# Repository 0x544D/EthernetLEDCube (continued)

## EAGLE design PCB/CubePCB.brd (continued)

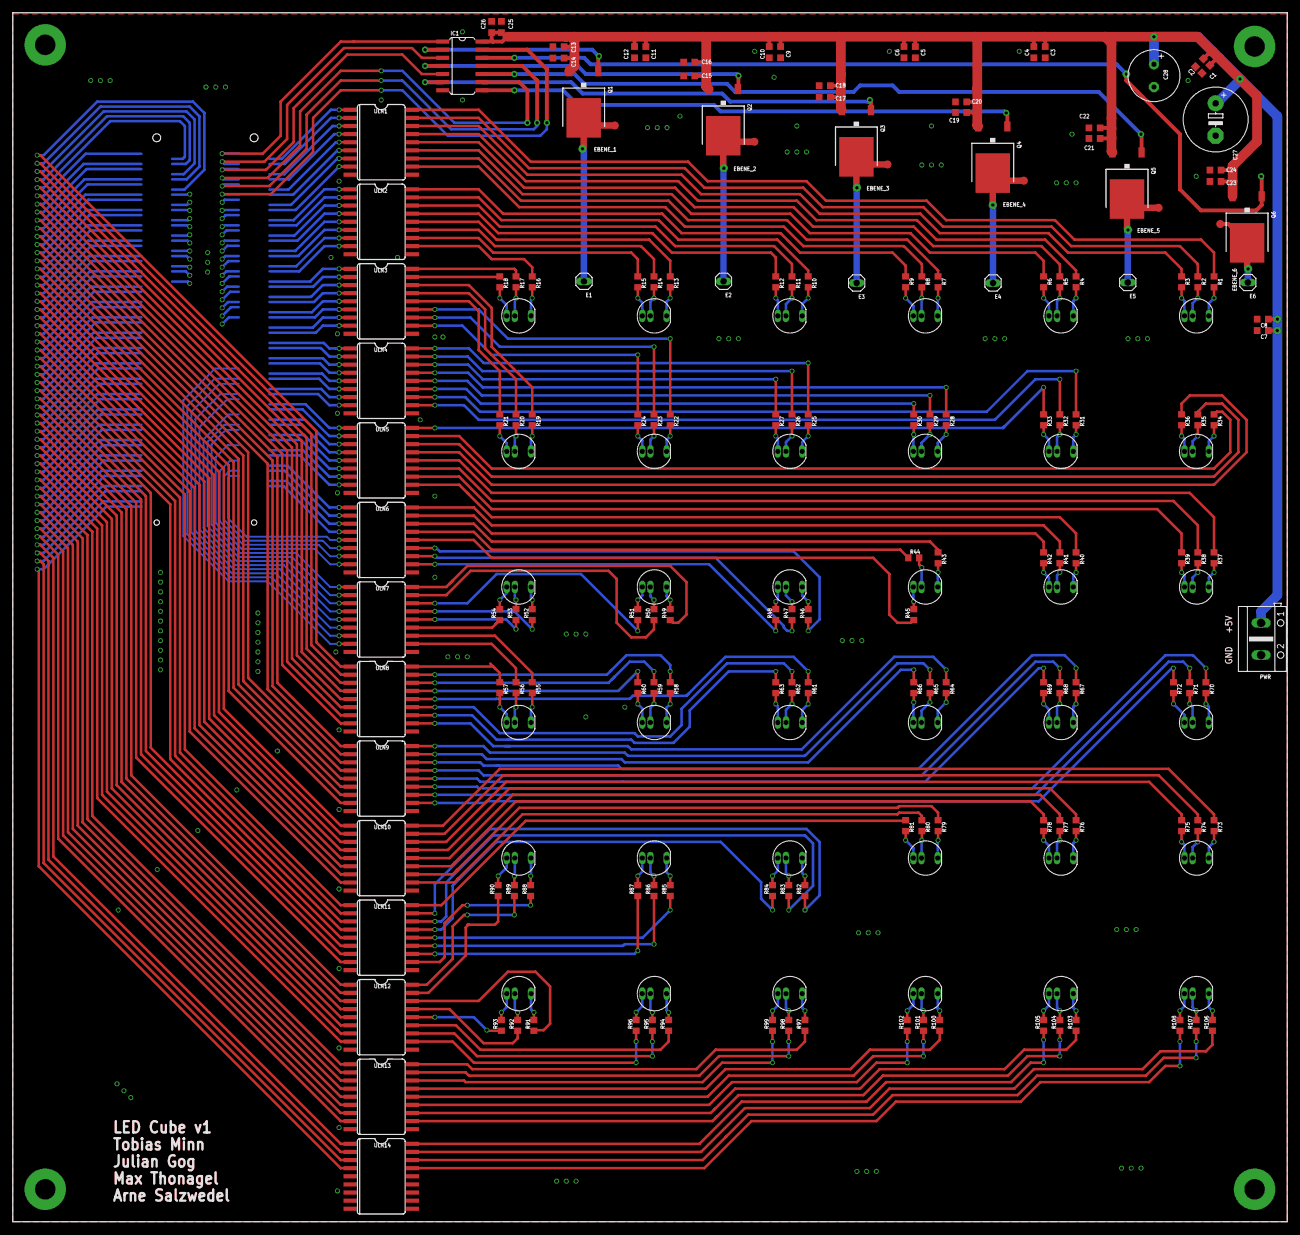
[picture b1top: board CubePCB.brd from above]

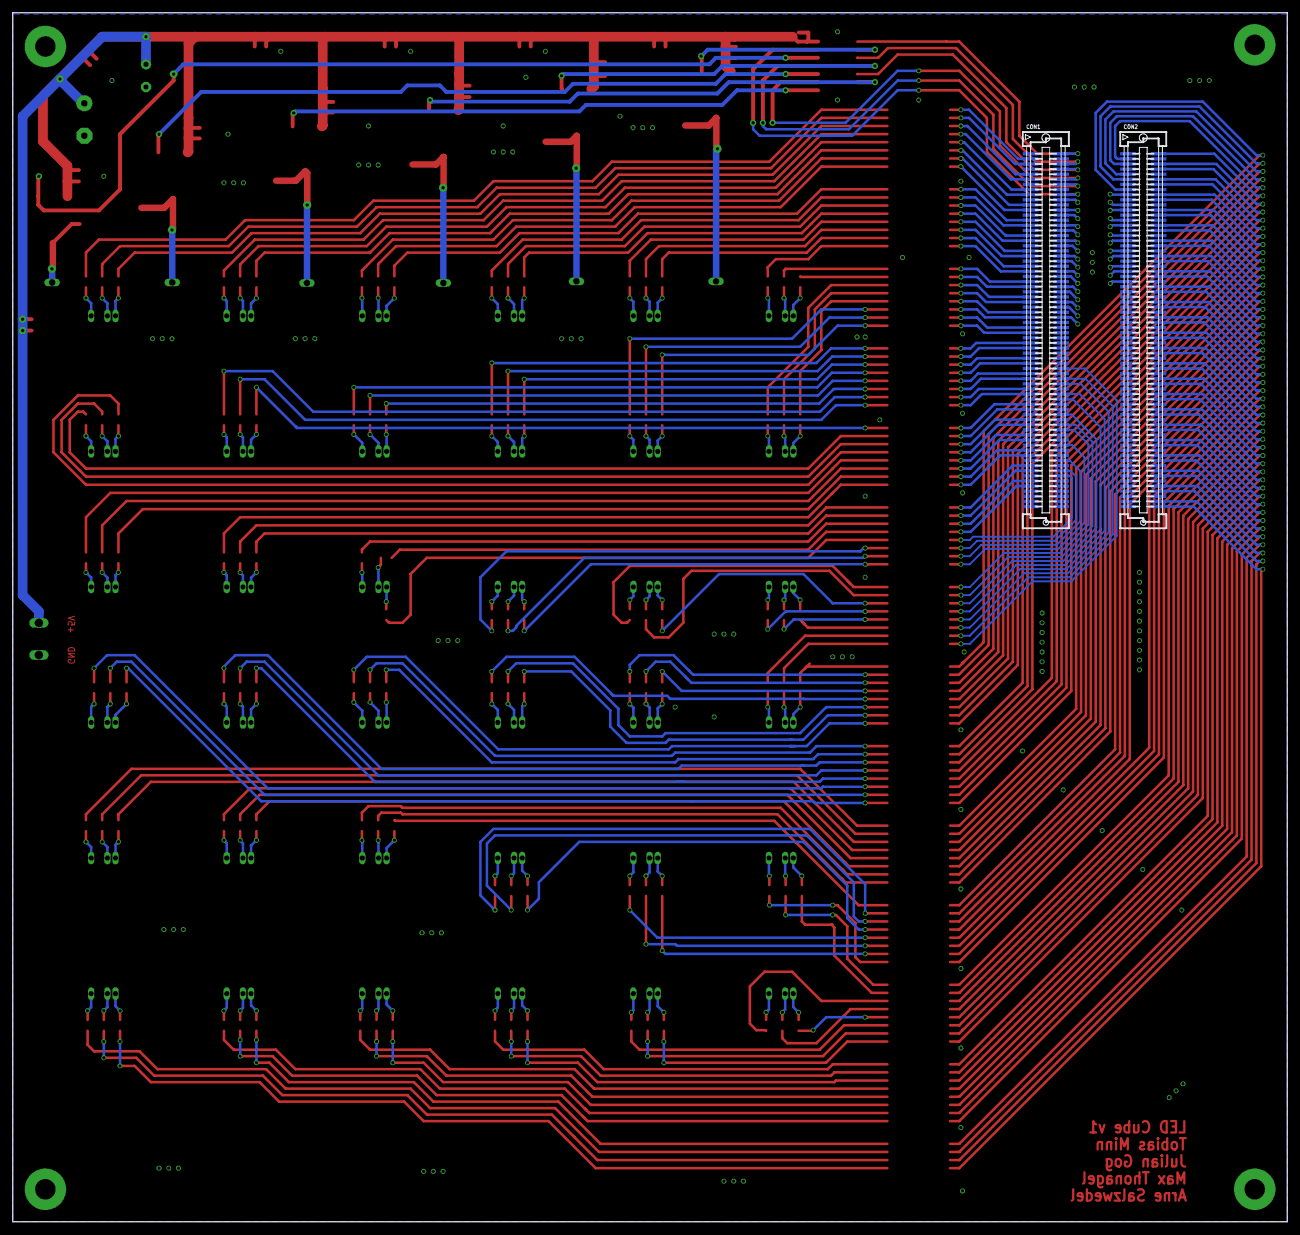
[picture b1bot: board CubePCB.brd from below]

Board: 2 copper layers, 199.4 x 189.2 mm, 208 parts (2 on the bottom side), 348 nets.

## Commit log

2018-07-08 added pictures
